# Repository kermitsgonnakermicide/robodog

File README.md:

# OpenDoggo

A quadruped robot platform running ROS2 Humble on a Raspberry Pi 4 with 3DOF legs and an optional SLAM capability via either Lidar and stereo vision.<br>

**Design**<br>
I started off by CADing the entire thing, keeping in mind that this will be an actively developed platform — no fancy covers, just raw plate and servo mounts.<br>
Went with a central plate that houses all the power distribution + electronics, and simple oval-style end mounts for the legs.<br>
The legs are 3DOF and use MG996R servos — cheap and decently powerful<br>
<br>

Later added a lid to keep things _mostly_ protected.<br>
<br>

**Electronics**<br>
I made a custom, 63 by 48 mm PCBA that has 5 major functions:<BR>

- step down power from my 4s 14.8v lipo battery to 5v<br>
- step up power from 5v to 7v to effectively power my servoes
- output that 5v power to my raspi on USB<br>
- control my servoes with a PCA9685<br>
- one of the best IMUs, the BNO086 for optimizing gait<br>

**Firmware**<br>
**ROS Packages**  
The whole ROS workspace is structured into 4 main packages:

- **servo_driver**  
  The hardware interface layer. This node communicates with one or more PCA9685 boards via I2C to send position signals to each servo motor. It exposes a simple ROS2 service + topic interface that allows other nodes to command joint angles (in degrees or radians). It also implements basic limits, deadzone filtering, and optional torque hold toggling. Each servo is mapped to a specific joint name and leg index.

- **leg_walker**  
  This package does all the IK heavy lifting. It:

  - Subscribes to target paw positions (either via a `/cmd_paw_pos` topic or internal walking scripts)
  - Solves 3DOF inverse kinematics per leg (coxa, femur, tibia)
  - Publishes joint angles to the `servo_driver`
  - Supports gait generation — currently just a trot gait, but it's modular
  - Includes walking state machines, leg timing, and paw trajectory interpolation
    This is where all the math happens.

- **slam_yplidar_x2**  
  SLAM package using the YDLidar X2. It launches:

  - A serial connection to the Lidar via `ydlidar_ros2_driver`
  - `slam_toolbox` in synchronous mode
  - RViz config for map + robot visualization
    Outputs a 2D occupancy map and robot pose estimate. Currently uses fake odom + map merging but will be upgraded later with IMU + gait odometry.

- **slam_stereo_picams**  
  Alternate SLAM method using two Raspberry Pi cameras as a stereo pair (synced via GPIO trigger). It:
  - Captures stereo image pairs
  - Runs semi-global block matching or other stereo algorithm (WIP: OpenCV + rtabmap)
  - Feeds into `rtabmap_ros` for visual SLAM
  - Outputs a 3D point cloud and pose estimate
    This is mostly experimental right now but promising for GPS-denied areas and outdoor mapping.

<br>

**NOTE**: Reusing the lipo battery from a diff project<br>

**BOM**
|ITEM |QTY|TOTAL |SRC |NOTES |
|-----------------------|---|------|----------------------------------------------------------------------------------------------------------------------------------------------------------------------------------------------------------------------------------------------------------------------------------------------------------------------------------------------------------------------------------------------------------------------------------------------------------------------------------------------------------------------|-----------------------------------------------------------------------------------------------------------------------------|
|Raspberry Pi 5 8GB |1 |94.82 |https://www.silverlineelectronics.in/collections/raspberry-pi-5-official-accessories/products/raspberry-pi-5-model-b-8gb-ram |I require an 8GB because I dont just need to use ROS - within it, I also need to do SLAM(even more computationally expensive)|
|RPi 5 Active Cooler |1 |5.27 |https://www.silverlineelectronics.in/collections/raspberry-pi-cooling-tech | |
|SD Card |1 |6.93 |https://www.amazon.in/SAMSUNG-Adaptor-Expanded-Storage-MB-MC64SA/dp/B0CXJ5Q222/ref=sr_1_3?crid=2JX27GGIJJTGI&dib=eyJ2IjoiMSJ9.W0mEzbMqa_UC3GB83swgkYea9f_3bRa4nMoh5j8uNEkChp42zWEkQpLMc0DnmWqmeu-AuuhK89UciyKu_5SFswRarCA-pBkkO60Q20oIBA_fkTCwYzRS_bEmYCP8yWifGQWiN7IS3pzrRxGHj_bR59EVNZ7nKRTTJQgCTymu6a5_LKu5mFX9u4Qt-aeNY8PHtSEAPnHDRGtQwz8awrEL67j54Ov63FOAKBYw6o2EqSo.z2cyXBa8m8xP1fLej5w40OuPwxTdFYv78CPP1mV_vY4&dib_tag=se&keywords=64gb+sd+card+evo&qid=1750190942&sprefix=64gb+sd+card+evo,aps,226&sr=8-3&th=1| |
|Waveshare Stereo Camera|1 |47.76 |https://hubtronics.in/imx219-83-stereo-camera | |
|YDLIDAR X2 |1 |60.99 |https://www.electronicscomp.com/ydlidar-x2-360-degree-ros-scanner-for-navigation-collision-avoidance-8m?srsltid=AfmBOorwLINheGIH6_5-cDKKJgGNAVWmLa5pv0aLsJ3wuyl8X8SN1hhzP3Q&gRefinements=SORT_BY:Price:+low+to+high | |
|PCBA |1 |129 |https://hc-cdn.hel1.your-objectstorage.com/s/v3/cd5c9a744fc6b144acc7592c6a4c4ebfb7888e05_image.png |LionCircuits |
|XT60PW-m |1 |1.91 |https://www.drkstore.in/amass-xt60pw-f20-connector/ |Not available to procure on LionCircuits, also including delivery |
|USB A |1 |0.17 |https://robu.in/product/u221-041n-1wr69-s5-xkb-1-5a-1-4p-female-40%e2%84%8385%e2%84%83-type-a-plugin-usb-connectors-rohs/ |Will cover myself, not available on LionCircuits |
|MG996R |12 |48.62 |https://sharvielectronics.com/product/mg996r-metal-gear-servo-motor/?srsltid=AfmBOoqSlyks-1TuudDgubd_qj9fNCwaQsQTs6MFmUkCxiBuGM9Gln68fNU | |
| | | | | |
| | | | | |
| | |395.47| | |
**NOTE: Will also cover the MG996s myself to ensure that i'm under budget**

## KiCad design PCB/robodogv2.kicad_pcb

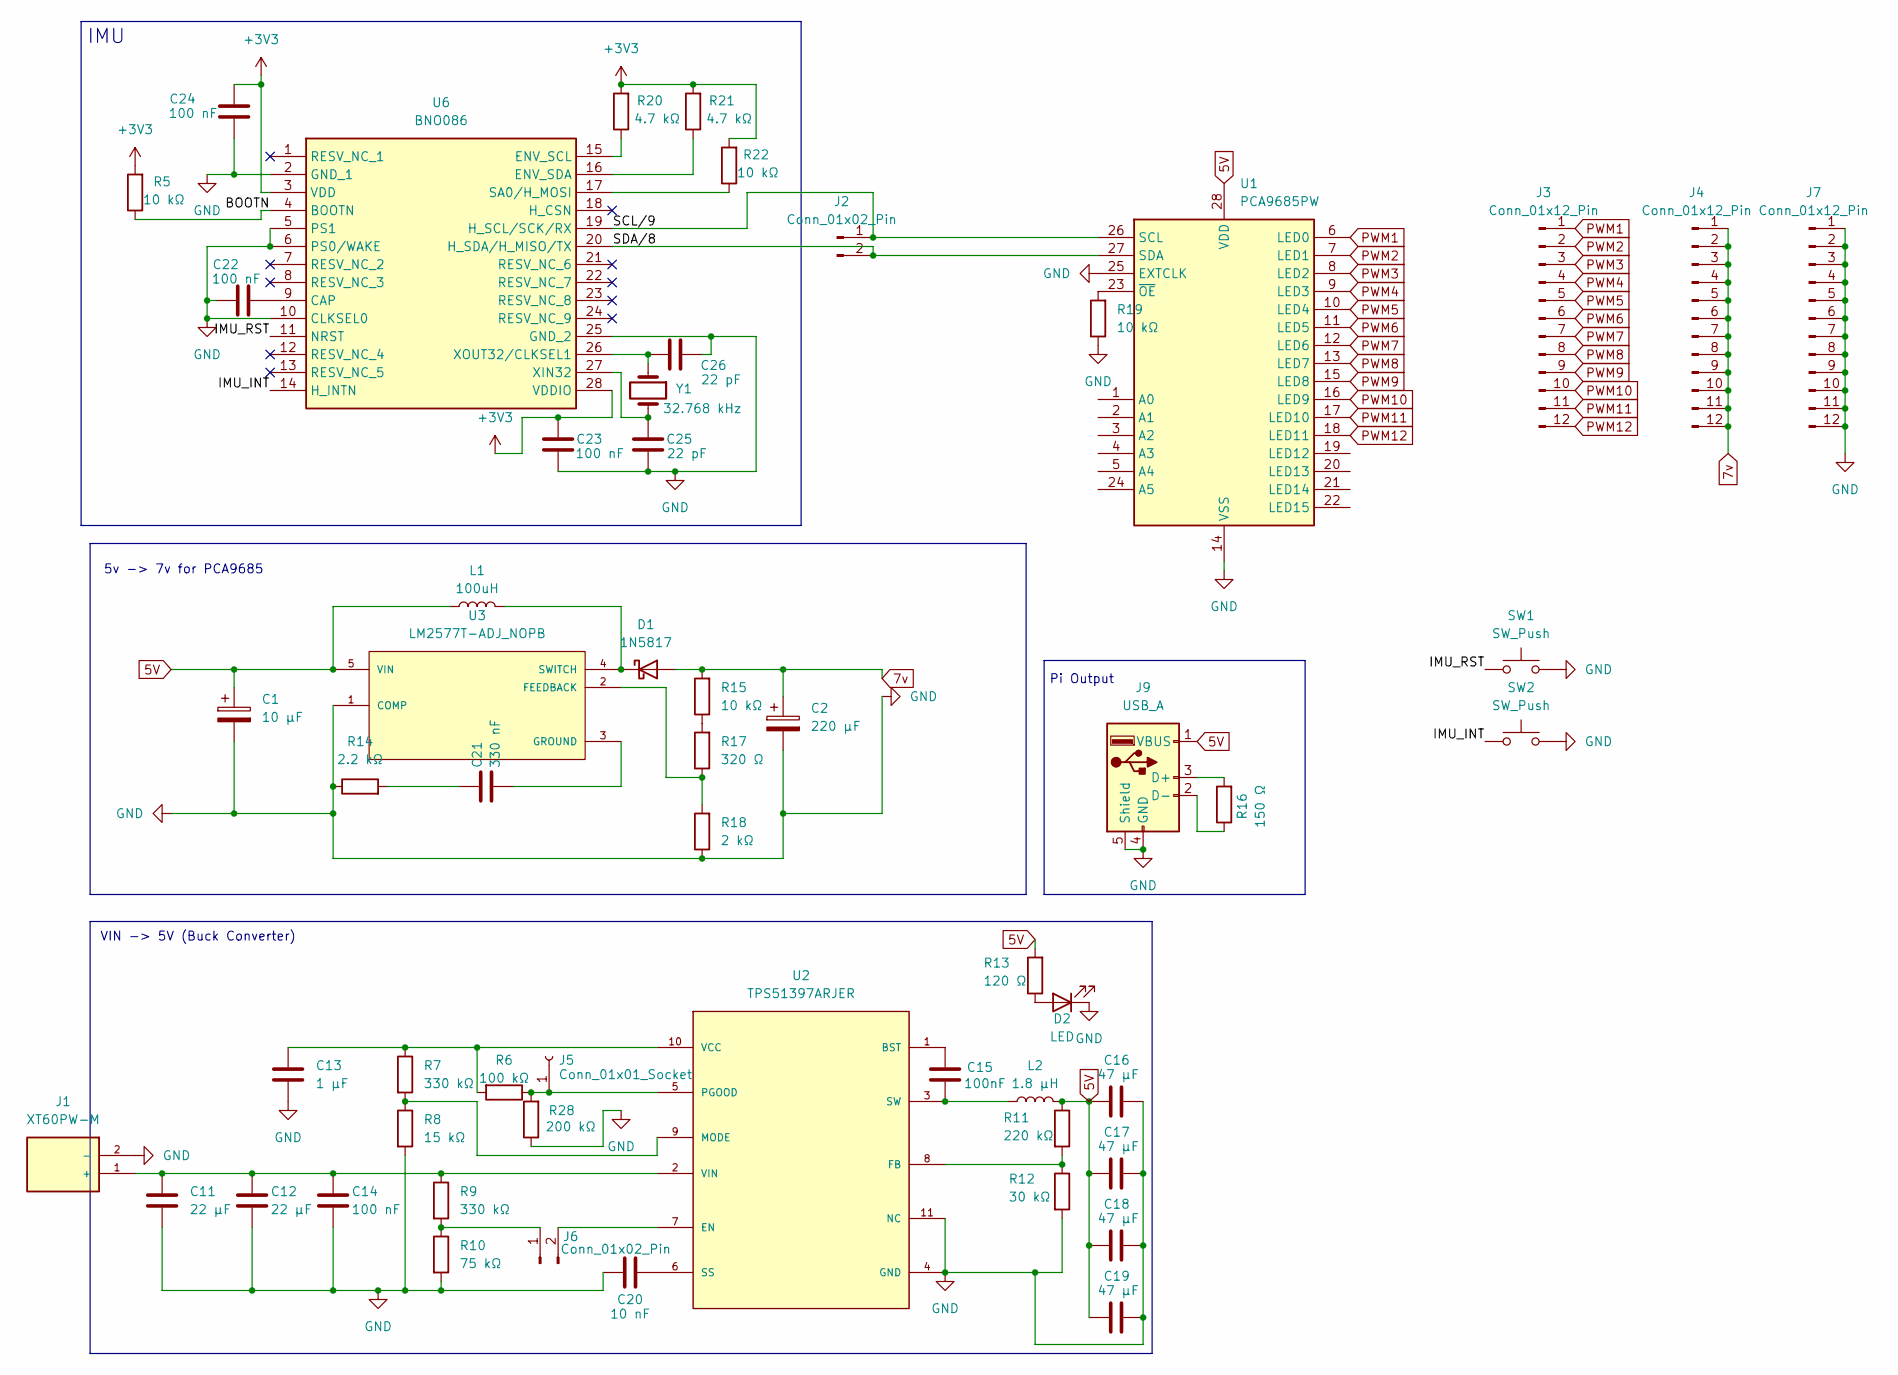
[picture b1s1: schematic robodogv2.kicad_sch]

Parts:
C1: 10 μF; CP_Elec_3x5.3
C2: 220 μF; CP_Elec_3x5.3
C11, C12: 22 μF; C_1206_3216Metric
C13: 1 μF; C_0402_1005Metric
C14: 100 nF; C_0805_2012Metric
C15: 100nF; C_0805_2012Metric
C16, C17, C18, C19: 47 μF; C_1206_3216Metric
C20: 10 nF; C_0805_2012Metric
C21: 330 nF; C_0805_2012Metric
C22, C23, C24: 100 nF; C_0402_1005Metric
C25, C26: 22 pF; C_0402_1005Metric
D1: 1N5817; D_0603_1608Metric
D2: LED; LED_0603_1608Metric
J1: XT60PW-M; AMASS_XT60PW-M; PARTREV V1.2
J2, J6: Conn_01x02_Pin; PinHeader_1x02_P2.54mm_Vertical
J3, J4, J7: Conn_01x12_Pin; PinHeader_1x12_P2.54mm_Vertical
J5: Conn_01x01_Socket; PinSocket_1x01_P2.54mm_Vertical
J9: USB_A; USB_A_Connfly_DS1095
L1: 100uH; L_0201_0603Metric
L2: 1.8 μH; IND_IHLP_5050_FD_VIS
R5, R22: 10 kΩ; R_0402_1005Metric
R6: 100 kΩ; R_0805_2012Metric
R7, R9: 330 kΩ; R_0603_1608Metric
R8: 15 kΩ; R_0603_1608Metric
R10: 75 kΩ; R_0603_1608Metric
R11: 220 kΩ; R_0805_2012Metric
R12: 30 kΩ; R_0805_2012Metric
R13: 120 Ω; R_0805_2012Metric
R14: 2.2 kΩ; R_0603_1608Metric
R15, R19: 10 kΩ; R_0603_1608Metric
R16: 150 Ω; R_0805_2012Metric
R17: 320 Ω; R_0603_1608Metric
R18: 2 kΩ; R_0603_1608Metric
R20, R21: 4.7 kΩ; R_0402_1005Metric
R28: 200 kΩ; R_0805_2012Metric
SW1, SW2: SW_Push; SW_Push_1P1T_NO_CK_KMR2
U1: PCA9685PW; TSSOP-28_4.4x9.7mm_P0.65mm
U2: TPS51397ARJER; RJE0020B-MFG
U3: LM2577T-ADJ_NOPB; VREG_LM2577T-ADJ_NOPB; PARTREV D
U6: BNO086; IC_BNO086
Y1: 32.768 kHz; Crystal_SMD_MicroCrystal_CC8V-T1A-2Pin_2.0x1.2mm

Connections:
5V: C1.1, C16.1, C17.1, C18.1, C19.1, J9.1 (VBUS), L1.1, L2.2, R11.1, R13.2, U1.28 (VDD), U3.5 (VIN)
7v: C2.1, D1.2 (A), J4.1, J4.2, J4.3, J4.4, J4.5, J4.6, J4.7, J4.8, J4.9, J4.10, J4.11, J4.12, R15.2
+3V3: C23.1, C24.2, R5.2, R20.2, R21.2, R22.2, U6.3 (VDD), U6.28 (VDDIO)
/BOOTN: R5.1, U6.4 (BOOTN)
/IMU_INT: SW2.1, U6.14 (H_INTN)
/IMU_RST: SW1.1, U6.11 (NRST)
/SCL/9: J2.1, U1.26 (SCL), U6.19 (H_SCL/SCK/RX)
/SDA/8: J2.2, U1.27 (SDA), U6.20 (H_SDA/H_MISO/TX)
GND: C1.2, C2.2, C11.1, C12.1, C13.2, C14.2, C16.2, C17.2, C18.2, C19.2, C20.2, C22.1, C23.2, C24.1, C25.2, C26.2, D2.1 (K), J1.2 (-), J7.1, J7.2, J7.3, J7.4, J7.5, J7.6, J7.7, J7.8, J7.9, J7.10, J7.11, J7.12, J9.4 (GND), J9.5 (Shield), R8.2, R10.2, R12.2, R14.1, R18.1, R19.1, R28.1, SW1.2, SW2.2, U1.14 (VSS), U1.25 (EXTCLK), U2.4 (GND), U2.11 (NC), U3.1 (COMP), U6.2 (GND_1), U6.5 (PS1), U6.6 (PS0/WAKE), U6.10 (CLKSEL0), U6.25 (GND_2)
unnamed: C21.1, R14.2
unnamed: D1.1 (K), L1.2, U3.4 (SWITCH)
unnamed: D2.2 (A), R13.1
unnamed: C11.2, C12.2, C14.1, J1.1 (+), R9.1, U2.2 (VIN)
unnamed: J5.1, R6.1, R28.2, U2.5 (PGOOD)
unnamed: J6.1, R9.2, R10.1
unnamed: J6.2, U2.7 (EN)
unnamed: J9.3 (D+), R16.2
unnamed: J9.2 (D-), R16.1
unnamed: R15.1, R17.2
unnamed: R19.2, U1.23 (~OE)
unnamed: C15.2, U2.1 (BST)
unnamed: R11.2, R12.1, U2.8 (FB)
unnamed: R7.2, R8.1, U2.9 (MODE)
unnamed: C20.1, U2.6 (SS)
unnamed: C15.1, L2.1, U2.3 (SW)
unnamed: C13.1, R6.2, R7.1, U2.10 (VCC)
unnamed: R17.1, R18.2, U3.2 (FEEDBACK)
unnamed: C21.2, U3.3 (GROUND)
unnamed: C22.2, U6.9 (CAP)
unnamed: R20.1, U6.15 (ENV_SCL)
unnamed: R21.1, U6.16 (ENV_SDA)
unnamed: R22.1, U6.17 (SA0/H_MOSI)
unnamed: C25.1, U6.27 (XIN32), Y1.2
unnamed: C26.1, U6.26 (XOUT32/CLKSEL1), Y1.1
PWM1: J3.1, U1.6 (LED0)
PWM2: J3.2, U1.7 (LED1)
PWM3: J3.3, U1.8 (LED2)
PWM4: J3.4, U1.9 (LED3)
PWM5: J3.5, U1.10 (LED4)
PWM6: J3.6, U1.11 (LED5)
PWM7: J3.7, U1.12 (LED6)
PWM8: J3.8, U1.13 (LED7)
PWM9: J3.9, U1.15 (LED8)
PWM10: J3.10, U1.16 (LED9)
PWM11: J3.11, U1.17 (LED10)
PWM12: J3.12, U1.18 (LED11)

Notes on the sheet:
5v -> 7v for PCA9685
VIN -> 5V (Buck Converter)
IMU
Pi Output

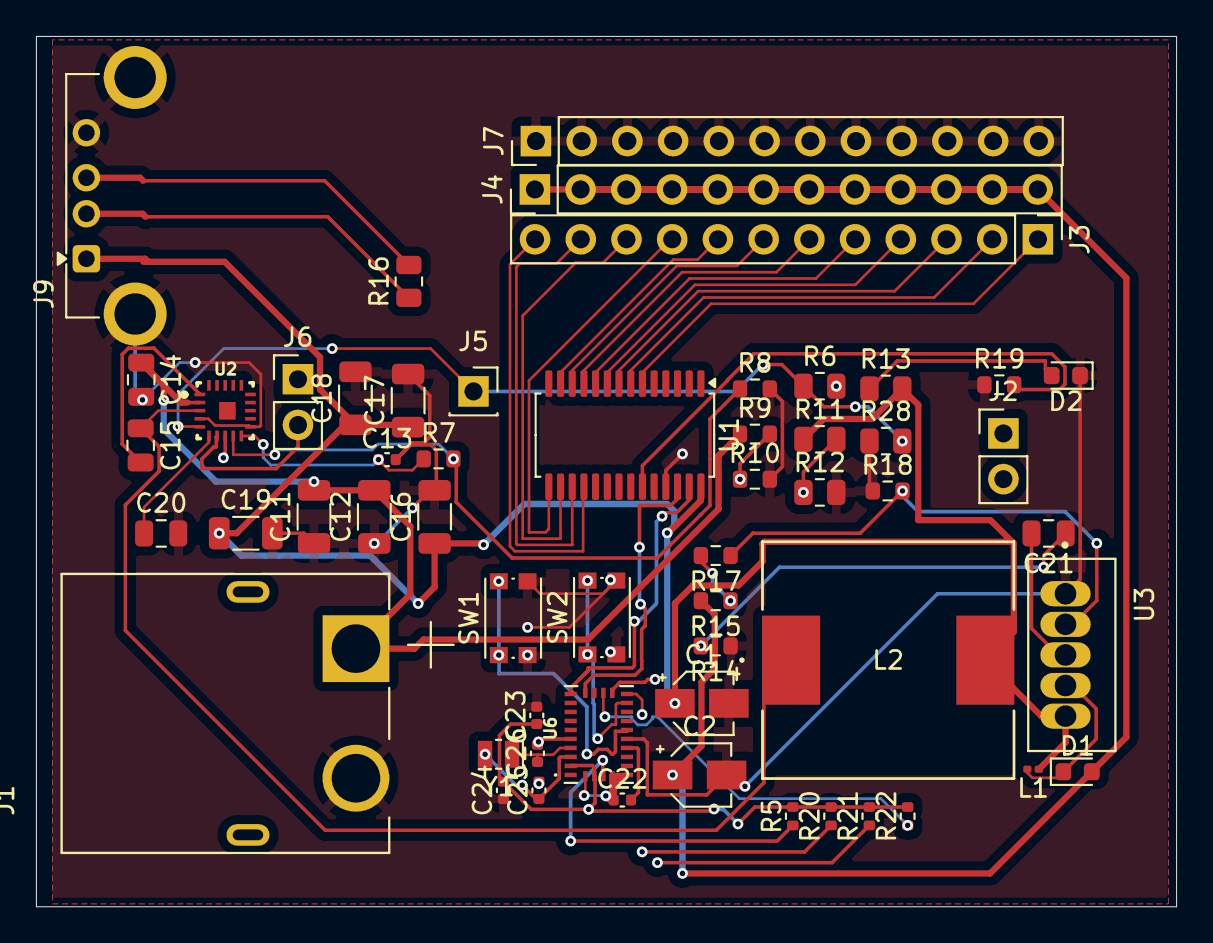
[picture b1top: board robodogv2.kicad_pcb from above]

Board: 4 copper layers, 63.3 x 48.3 mm, 56 parts (0 on the bottom side), 46 nets.

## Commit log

2025-06-11 placeholders for now
2025-06-17 baguette
2025-06-17 bagueete
2025-06-17 FUNWARE FINALYY YEYAYAYAYAYAYA
2025-06-23 finaalalalalaaaaaaaaaaaaaaa!!!!
    baguettee
